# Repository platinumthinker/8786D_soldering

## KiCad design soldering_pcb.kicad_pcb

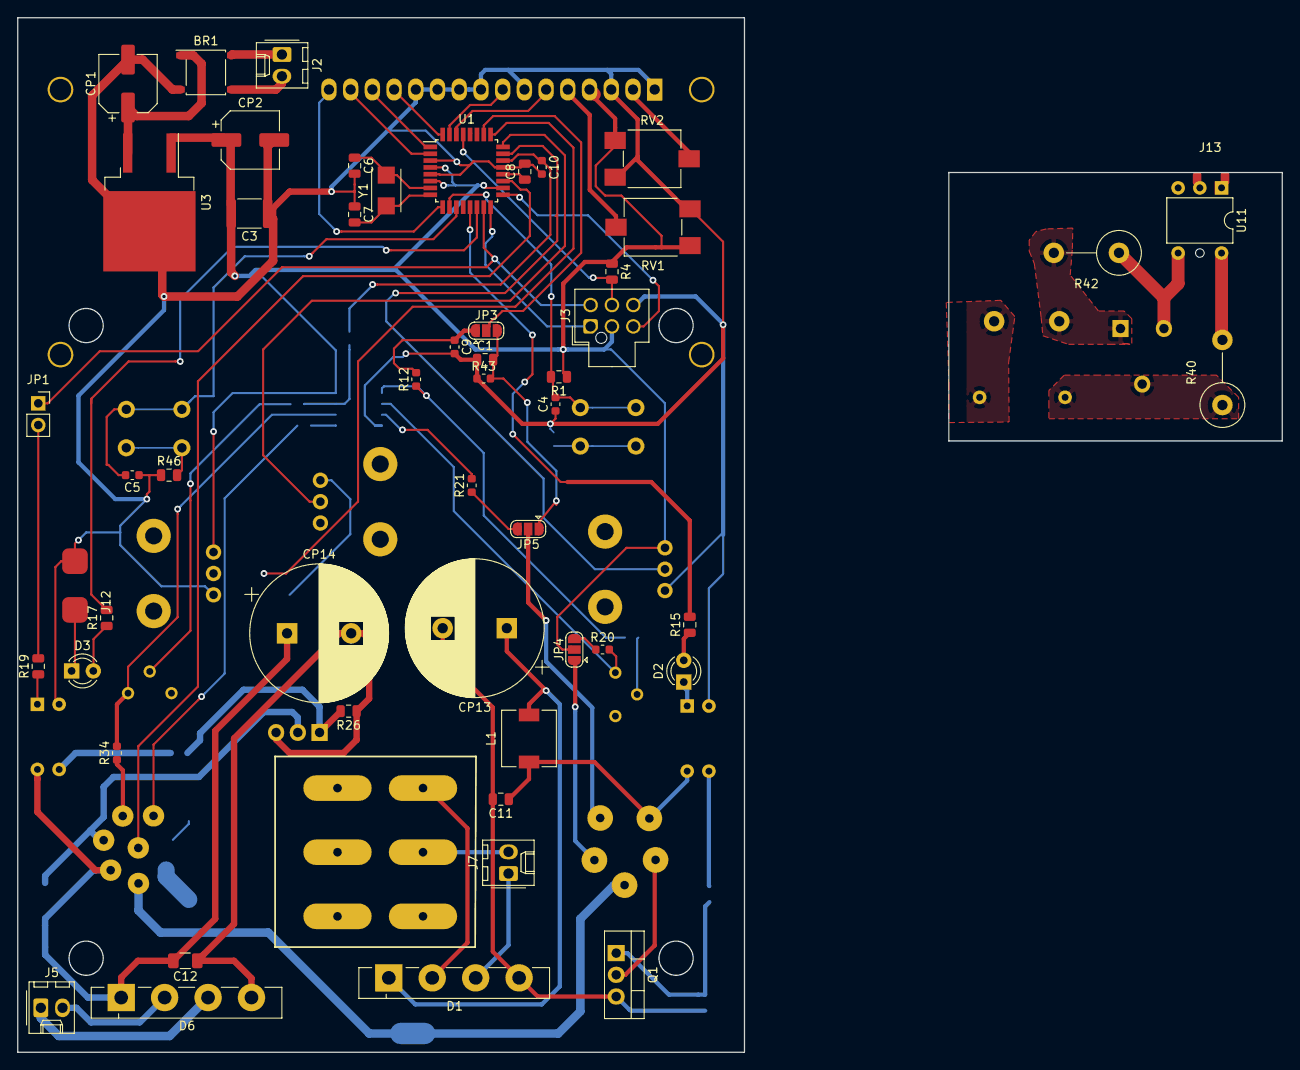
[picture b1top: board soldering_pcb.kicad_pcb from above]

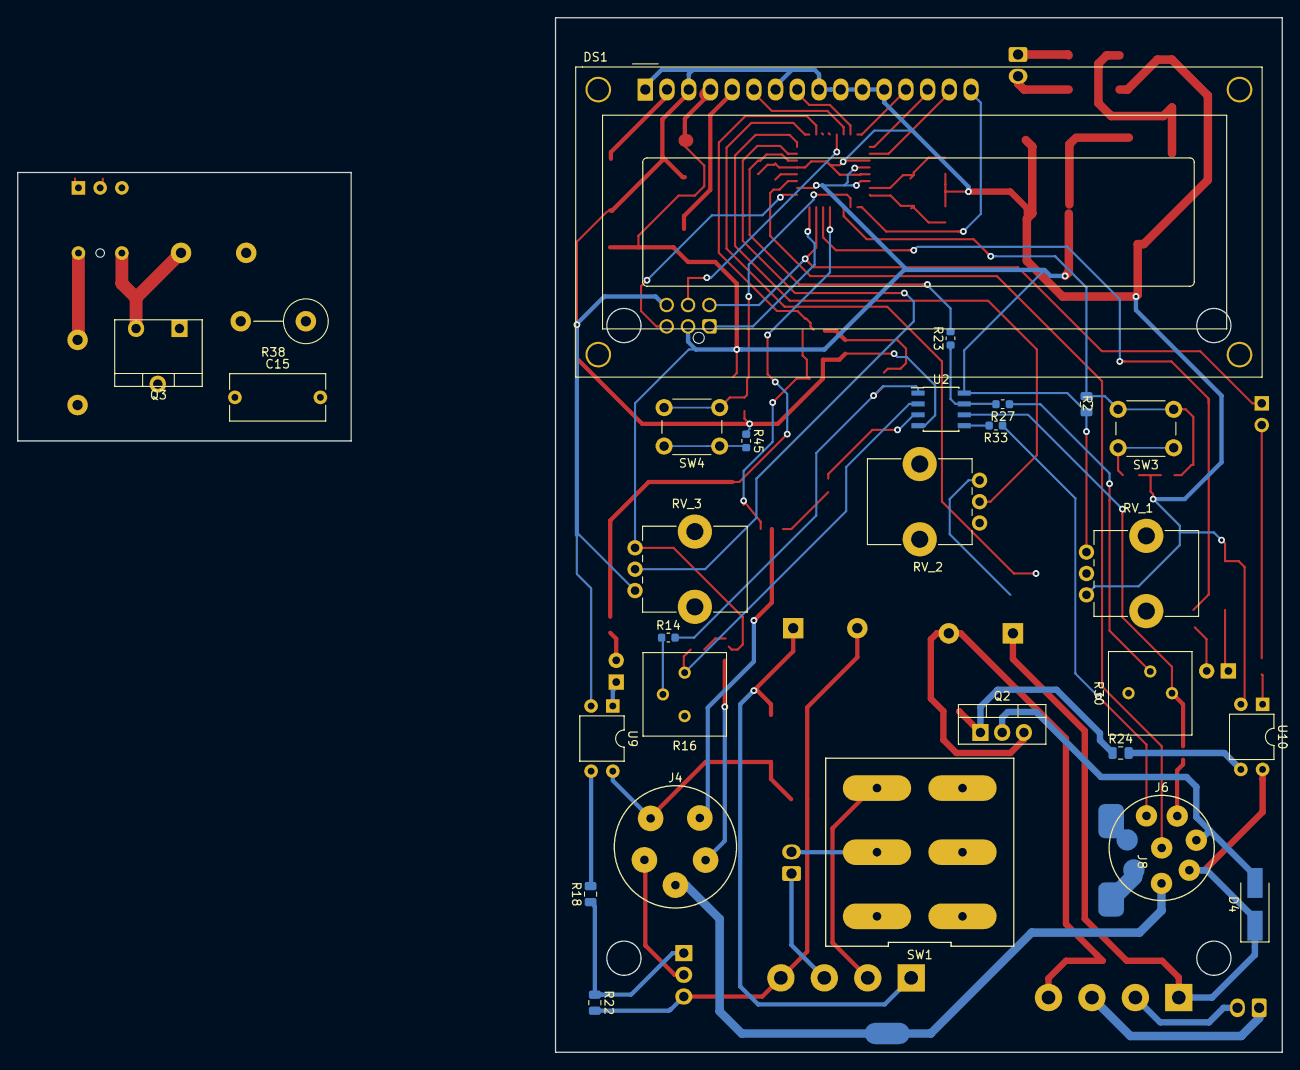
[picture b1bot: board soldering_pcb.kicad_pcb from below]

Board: 2 copper layers, 147.9 x 121.0 mm, 81 parts (29 on the bottom side), 80 nets.

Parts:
BR1: SDB107-TP; Diode_Bridge_Diotec_ABS
C1: 10nF; C_0805_2012Metric
C3: 100nF; C_1812_4532Metric
C4, C5, C9, C10: 0.1u; C_0603_1608Metric
C6, C7: 22pF; C_0805_2012Metric
C8, C11: 100nF; C_0805_2012Metric
C12: 100nF; C_1206_3216Metric
C15: 0.01uF/230v; C_Rect_L11.0mm_W5.3mm_P10.00mm_MKT
CP1, CP2: 100uF; CP_Elec_6.3x5.4
CP13, CP14: 2200uF; CP_Radial_D16.0mm_P7.50mm
D1, D6: GBU8A; Diode_Bridge_Vishay_GBU
D2, D3: LED; LED_D3.0mm
D4: 1N5400; D_SMA_Handsoldering
DS1: HY1602E; WC1602A
J2: power_in2_10v; Molex_KK-254_AE-6410-02A_1x02_P2.54mm_Vertical
J3: ISP; Molex_Nano-Fit_105310-xx06_2x03_P2.50mm_Vertical
J4: Main Solder Out; GX16-5
J5: power_in2_26v; Molex_KK-254_AE-6410-02A_1x02_P2.54mm_Vertical
J6: Rework Solder Out; GX-16-8
J7: power_in2_24v; Molex_KK-254_AE-6410-02A_1x02_P2.54mm_Vertical
J8: heat; conn_clear_02x01
J12: Conn_01x02_Female; conn_clear_02x01
J13: Conn_01x02_Male; small_conn_clear_02x01
JP1: Prog; PinSocket_1x02_P2.54mm_Vertical
JP3: JP_TH3; SolderJumper-3_P1.3mm_Open_RoundedPad1.0x1.5mm
JP4: JP_TH1; SolderJumper-3_P1.3mm_Open_RoundedPad1.0x1.5mm
JP5: JP_TH2; SolderJumper-3_P1.3mm_Open_RoundedPad1.0x1.5mm
L1: 300uH; L_6.3x6.3_H3
Q1, Q2: IRF3205; TO-220-3_Vertical
Q3: BT139-600; TO-220-3_Vertical_power
R1, R2, R4: 10k; R_0805_2012Metric
R12, R23: 10k; R_0603_1608Metric
R14, R27: 100k; R_0603_1608Metric
R15, R17, R19: 220; R_0805_2012Metric
R16, R30: 50k; Potentiometer_Bourns_3386P_Vertical
R18, R24: 100; R_0805_2012Metric
R20, R21, R33, R34, R45: 1k; R_0603_1608Metric
R22, R26, R46: 1k; R_0805_2012Metric
R38: 39; R_Axial_DIN0516_L15.5mm_D5.0mm_P7.62mm_Vertical
R40: 390; R_Axial_DIN0516_L15.5mm_D5.0mm_P7.62mm_Vertical
R42: 300; R_Axial_DIN0516_L15.5mm_D5.0mm_P7.62mm_Vertical
R43: 4k7; R_0603_1608Metric
RV1, RV2: 10k; Potentiometer_ACP_CA6-VSMD_Vertical
RV_1, RV_2, RV_3: 10k; Potentiometer_Alps_RK09K_Single_Vertical
SW1: SW_SPDT2; SWICH
SW3: LEFT_BTN; SW_PUSH_6mm
SW4: RIGHT_BTN; SW_PUSH_6mm
U1: ATmega8; TQFP-32_7x7mm_P0.8mm
U2: LM358; SOIC-8_3.9x4.9mm_P1.27mm
U3: LM7805_TO220; TO-263-2
U9, U10: SFH617A-2; DIP-4_W7.62mm
U11: MOC3041M; DIP-6_W7.62mm
Y1: 16Mhz; Crystal_SMD_Qantek_QC5CB-2Pin_5x3.2mm

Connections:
+5V: C3.2, CP2.1, DS1.4, J3.2, JP4.3, R1.1, R2.1, R4.1, RV1.3, RV2.3, RV_1.3, RV_2.3, RV_3.3, U1.4, U1.6, U1.18, U2.8, U3.1
/1: DS1.6, U1.30
/2: DS1.8, U1.31
/3: DS1.13, U1.32
/4: DS1.14, U1.1
/5: DS1.15, U1.2
/6: DS1.16, U1.9
/+: C12.2, CP14.1, D4.1, D6.1, J6.5, U10.4
/+24v: C11.1, J4.1, L1.1, U9.4
/-: C12.1, CP14.2, D6.4, Q2.3, R26.1
/PWM_MAIN_SOLDER: R15.2, U1.13
/PWM_REWORK_FAN: JP1.2, R19.2
/PWM_REWORK_HEAT: R17.2, U1.14
/gercon: J6.3, U1.19
/gnd_24v: C11.2, CP13.2, D1.4, Q1.3, R22.2
/term1: JP3.2, U1.26
/term2: C10.1, R23.2, U1.22
Earth: J4.3, J6.4
GNDA: BR1.2, C1.1, C3.1, C4.1, C5.1, C6.2, C7.1, C8.2, C9.2, C10.2, CP1.2, CP2.2, DS1.1, DS1.3, DS1.7, DS1.9, DS1.10, DS1.11, DS1.12, J3.6, J12.2, R43.1, R45.1, R46.1, RV1.1, RV2.1, RV_1.1, RV_2.1, RV_3.1, U1.3, U1.5, U1.21, U2.4, U3.2, U9.2, U10.2
MISO: J3.1, U1.16
MOSI: J3.4, JP1.1, U1.15
unnamed: BR1.1, CP1.1, U3.3
unnamed: BR1.3, J2.2
unnamed: BR1.4, J2.1
unnamed: C1.2, JP3.3, JP5.1, R43.2
unnamed: C4.2, R1.2, SW4.1, U1.10
unnamed: C5.2, R2.2, SW3.1, U1.11
unnamed: C6.1, U1.7, Y1.2
unnamed: C7.2, U1.8, Y1.1
unnamed: C8.1, U1.20
unnamed: C9.1, JP3.1, R12.2
unnamed: C15.1, Q3.2, R40.1
unnamed: C15.2, R38.1
unnamed: CP13.1, D1.1, L1.2
unnamed: D1.2, SW1.1
unnamed: D1.3, J7.1
unnamed: D2.1, U9.1
unnamed: D2.2, R15.1
unnamed: D3.1, J12.1
unnamed: D3.2, R17.1
unnamed: D4.2, J6.6, Q2.2
unnamed: D6.2, J5.2
unnamed: D6.3, J5.1
unnamed: DS1.2, RV2.2
unnamed: DS1.5, RV1.2
unnamed: J4.2, Q1.2
unnamed: J4.4, JP4.2
unnamed: J4.5, JP5.2
unnamed: J6.1, R33.1
unnamed: J6.2, R34.1
unnamed: J6.7, J8.2
unnamed: J6.8, J8.1
unnamed: J7.2, SW1.2
unnamed: J13.1, U11.1
unnamed: J13.2, U11.2
unnamed: JP4.1, R20.1
unnamed: JP5.3, R21.1
unnamed: Q1.1, R18.1, R22.1
unnamed: Q2.1, R24.1, R26.2
unnamed: Q3.1, R38.2, R42.2
unnamed: Q3.3, R42.1, U11.4
unnamed: R12.1, R14.2, U2.1
unnamed: R14.1, R16.2
unnamed: R16.1, R20.2, U2.2
unnamed: R18.2, U9.3
unnamed: R19.1, U10.1
unnamed: R21.2, U2.3
unnamed: R23.1, R27.2, U2.7
unnamed: R24.2, U10.3
unnamed: R27.1, R30.2
unnamed: R30.1, R34.2, U2.6
unnamed: R33.2, U2.5
unnamed: R40.2, U11.6
unnamed: R45.2, SW4.2
unnamed: R46.2, SW3.2
unnamed: RV_1.2, U1.25
unnamed: RV_2.2, U1.24
unnamed: RV_3.2, U1.23
RESET: J3.5, R4.2, U1.29
SCK: J3.3, U1.17

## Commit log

2019-04-04 Init
